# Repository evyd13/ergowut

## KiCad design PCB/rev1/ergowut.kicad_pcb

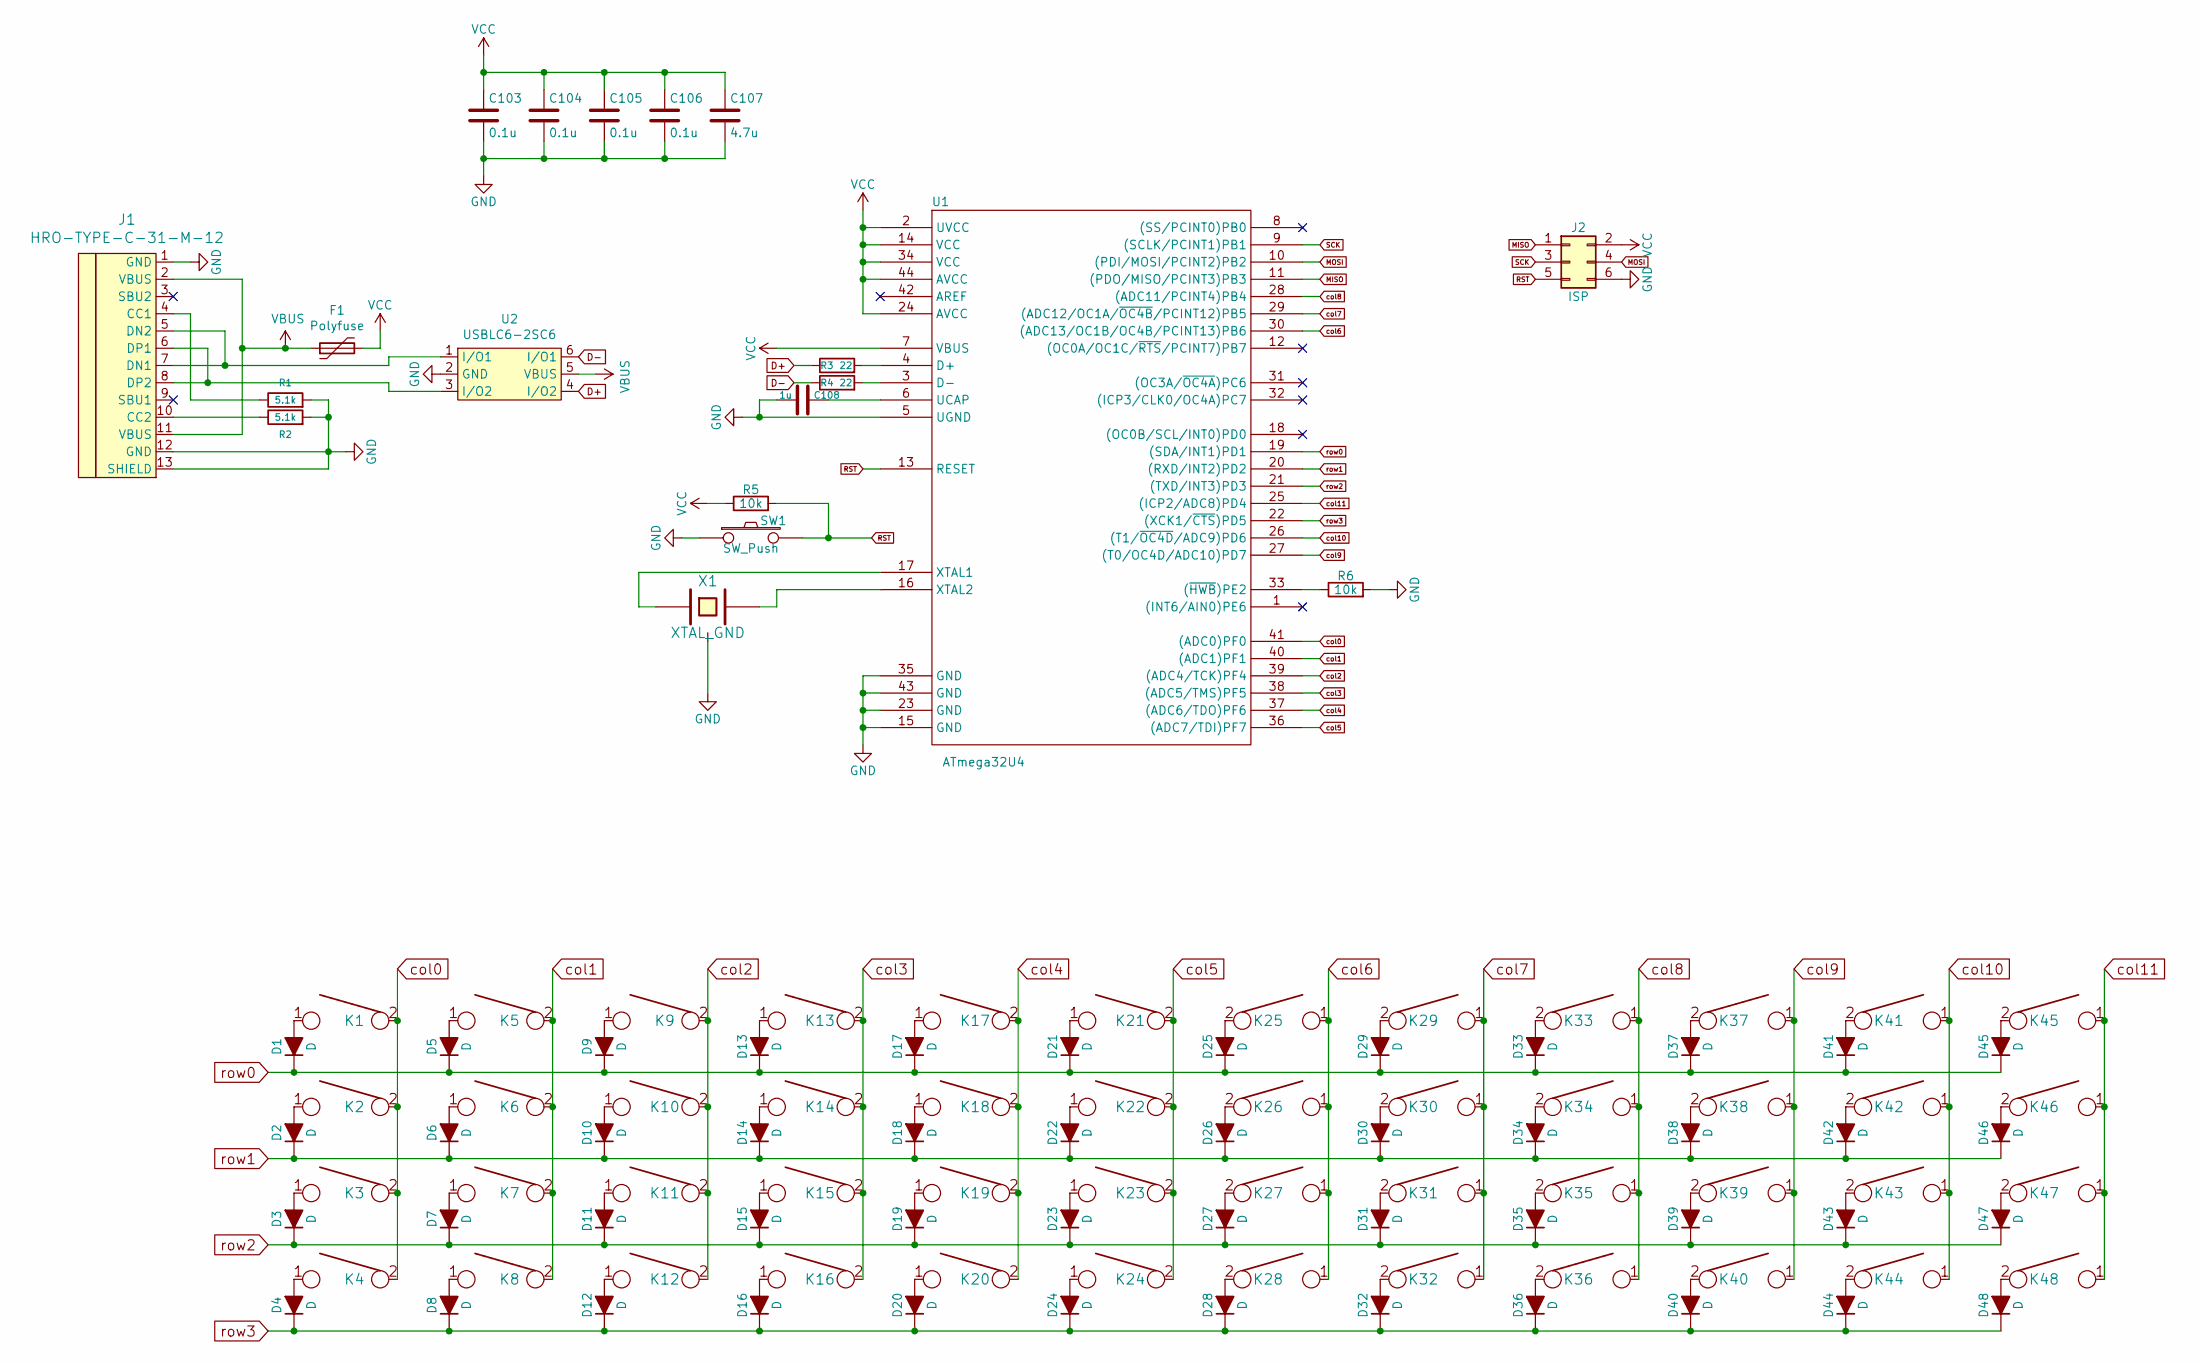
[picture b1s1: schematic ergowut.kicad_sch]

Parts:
C103, C104, C105, C106: 0.1u; C_0805
C107: 4.7u; C_0805
C108: 1u; C_0805
D1, D2, D3, D4, D5, D6, D7, D8, D9, D10, D11, D12, D13, D14, D15, D16, D17, D18, D19, D20, D21, D22, D23, D24, D25, D26, D27, D28, D29, D30, D31, D32, D33, D34, D35, D36, D37, D38, D39, D40, D41, D42, D43, D44, D45, D46, D47, D48: D; hybrid_DIODE_sans
F1: Polyfuse; F_0805
J1: HRO-TYPE-C-31-M-12
J2: ISP; isp_standard
K1, K2, K3, K4, K5, K6, K7, K8, K9, K10, K11, K12, K13, K14, K15, K16, K17, K18, K19, K20, K21, K22, K23, K25, K26, K27, K29, K30, K31, K32, K33, K34, K35, K36, K37, K38, K39, K40, K41, K42, K43, K44, K45, K46, K47, K48: KEYSW; CHERRY_PLATE_100H
K24, K28: KEYSW; CHERRY_PLATE_150H
R1, R2: 5.1k; R_0805
R3, R4: 22; R_0805
R5, R6: 10k; R_0805
SW1: SW_Push; SW_SPST_TL3342
U1: ATmega32U4; ATMEGA32U4
U2: USBLC6-2SC6
X1: XTAL_GND; Resonator_SMD_muRata_CSTNExxV-3Pin-p1.2

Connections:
D+: R3.1, U2.4 (I/O2)
D-: R4.1, U2.6 (I/O1)
GND: C103.2, C104.2, C105.2, C106.2, C107.2, C108.2, J1.1 (GND), J1.12 (GND), J1.13 (SHIELD), J2.6, R1.2, R2.2, R6.2, SW1.1, U1.5 (UGND), U1.15 (GND), U1.23 (GND), U1.35 (GND), U1.43 (GND), U2.2 (GND), X1.3
MISO: J2.1, U1.11 ((PDO/MISO/PCINT3)PB3)
MOSI: J2.4, U1.10 ((PDI/MOSI/PCINT2)PB2)
unnamed: C108.1, U1.6 (UCAP)
unnamed: D1.2 (A), K1.1
unnamed: D2.2 (A), K2.1
unnamed: D3.2 (A), K3.1
unnamed: D4.2 (A), K4.1
unnamed: D5.2 (A), K5.1
unnamed: D6.2 (A), K6.1
unnamed: D7.2 (A), K7.1
unnamed: D8.2 (A), K8.1
unnamed: D9.2 (A), K9.1
unnamed: D10.2 (A), K10.1
unnamed: D11.2 (A), K11.1
unnamed: D12.2 (A), K12.1
unnamed: D13.2 (A), K13.1
unnamed: D14.2 (A), K14.1
unnamed: D15.2 (A), K15.1
unnamed: D16.2 (A), K16.1
unnamed: D17.2 (A), K17.1
unnamed: D18.2 (A), K18.1
unnamed: D19.2 (A), K19.1
unnamed: D20.2 (A), K20.1
unnamed: D21.2 (A), K21.1
unnamed: D22.2 (A), K22.1
unnamed: D23.2 (A), K23.1
unnamed: D24.2 (A), K24.1
unnamed: D25.2 (A), K25.2
unnamed: D26.2 (A), K26.2
unnamed: D27.2 (A), K27.2
unnamed: D28.2 (A), K28.2
unnamed: D29.2 (A), K29.2
unnamed: D30.2 (A), K30.2
unnamed: D31.2 (A), K31.2
unnamed: D32.2 (A), K32.2
unnamed: D33.2 (A), K33.2
unnamed: D34.2 (A), K34.2
unnamed: D35.2 (A), K35.2
unnamed: D36.2 (A), K36.2
unnamed: D37.2 (A), K37.2
unnamed: D38.2 (A), K38.2
unnamed: D39.2 (A), K39.2
unnamed: D40.2 (A), K40.2
unnamed: D41.2 (A), K41.2
unnamed: D42.2 (A), K42.2
unnamed: D43.2 (A), K43.2
unnamed: D44.2 (A), K44.2
unnamed: D45.2 (A), K45.2
unnamed: D46.2 (A), K46.2
unnamed: D47.2 (A), K47.2
unnamed: D48.2 (A), K48.2
unnamed: J1.4 (CC1), R1.1
unnamed: J1.5 (DN2), J1.7 (DN1), U2.1 (I/O1)
unnamed: J1.6 (DP1), J1.8 (DP2), U2.3 (I/O2)
unnamed: J1.10 (CC2), R2.1
unnamed: R3.2, U1.4 (D+)
unnamed: R4.2, U1.3 (D-)
unnamed: R6.1, U1.33 ((~HWB~)PE2)
unnamed: U1.16 (XTAL2), X1.2
unnamed: U1.17 (XTAL1), X1.1
RST: J2.5, R5.2, SW1.2, U1.13 (RESET)
SCK: J2.3, U1.9 ((SCLK/PCINT1)PB1)
VBUS: F1.1, J1.2 (VBUS), J1.11 (VBUS), U2.5 (VBUS)
VCC: C103.1, C104.1, C105.1, C106.1, C107.1, F1.2, J2.2, R5.1, U1.2 (UVCC), U1.7 (VBUS), U1.14 (VCC), U1.24 (AVCC), U1.34 (VCC), U1.44 (AVCC)
col0: K1.2, K2.2, K3.2, K4.2, U1.41 ((ADC0)PF0)
col1: K5.2, K6.2, K7.2, K8.2, U1.40 ((ADC1)PF1)
col2: K9.2, K10.2, K11.2, K12.2, U1.39 ((ADC4/TCK)PF4)
col3: K13.2, K14.2, K15.2, K16.2, U1.38 ((ADC5/TMS)PF5)
col4: K17.2, K18.2, K19.2, K20.2, U1.37 ((ADC6/TDO)PF6)
col5: K21.2, K22.2, K23.2, K24.2, U1.36 ((ADC7/TDI)PF7)
col6: K25.1, K26.1, K27.1, K28.1, U1.30 ((ADC13/OC1B/OC4B/PCINT13)PB6)
col7: K29.1, K30.1, K31.1, K32.1, U1.29 ((ADC12/OC1A/~OC4B~/PCINT12)PB5)
col8: K33.1, K34.1, K35.1, K36.1, U1.28 ((ADC11/PCINT4)PB4)
col9: K37.1, K38.1, K39.1, K40.1, U1.27 ((T0/OC4D/ADC10)PD7)
col10: K41.1, K42.1, K43.1, K44.1, U1.26 ((T1/~OC4D~/ADC9)PD6)
col11: K45.1, K46.1, K47.1, K48.1, U1.25 ((ICP2/ADC8)PD4)
row0: D1.1 (K), D5.1 (K), D9.1 (K), D13.1 (K), D17.1 (K), D21.1 (K), D25.1 (K), D29.1 (K), D33.1 (K), D37.1 (K), D41.1 (K), D45.1 (K), U1.19 ((SDA/INT1)PD1)
row1: D2.1 (K), D6.1 (K), D10.1 (K), D14.1 (K), D18.1 (K), D22.1 (K), D26.1 (K), D30.1 (K), D34.1 (K), D38.1 (K), D42.1 (K), D46.1 (K), U1.20 ((RXD/INT2)PD2)
row2: D3.1 (K), D7.1 (K), D11.1 (K), D15.1 (K), D19.1 (K), D23.1 (K), D27.1 (K), D31.1 (K), D35.1 (K), D39.1 (K), D43.1 (K), D47.1 (K), U1.21 ((TXD/INT3)PD3)
row3: D4.1 (K), D8.1 (K), D12.1 (K), D16.1 (K), D20.1 (K), D24.1 (K), D28.1 (K), D32.1 (K), D36.1 (K), D40.1 (K), D44.1 (K), D48.1 (K), U1.22 ((XCK1/~CTS~)PD5)

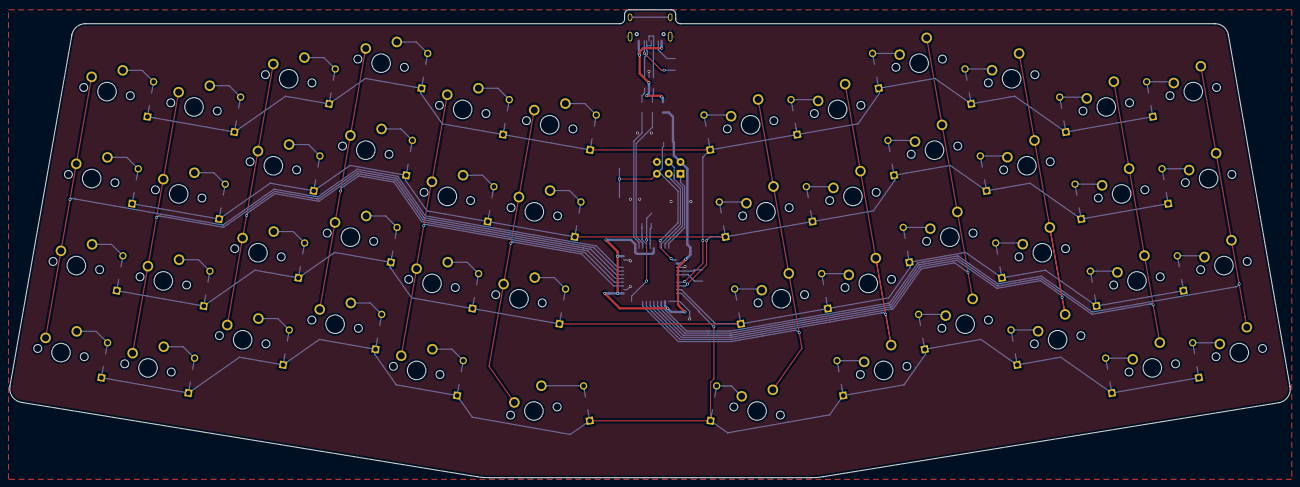
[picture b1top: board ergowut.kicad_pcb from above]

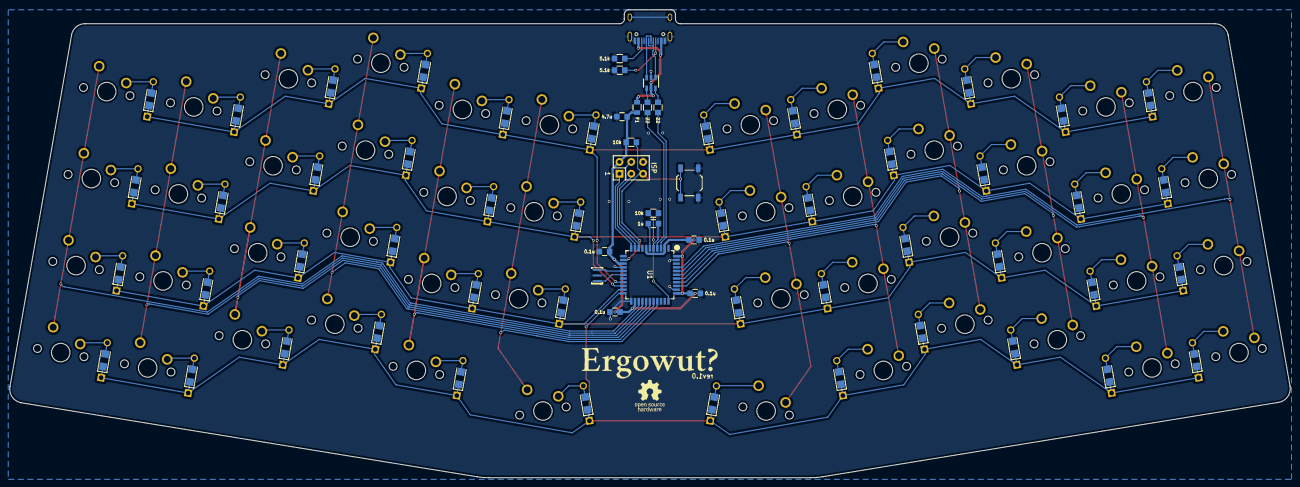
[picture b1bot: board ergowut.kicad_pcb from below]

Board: 2 copper layers, 275.4 x 100.6 mm, 115 parts (67 on the bottom side), 83 nets.

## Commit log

2020-12-27 add 3d model
